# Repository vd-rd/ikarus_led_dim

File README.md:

## DC/DC linear dimmer for Power LEDS
3d view of the board available [here](https://a360.co/2TdbULz)

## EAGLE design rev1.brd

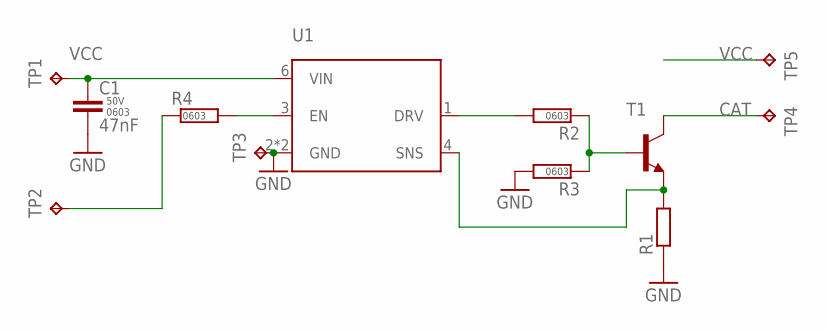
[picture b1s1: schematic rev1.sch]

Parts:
C1: 47nF; C0603; RATING 50V
R1: R-EU_R1206; R1206
R2, R3, R4: RES-0603; R0603
T1: BC868-NPN-SOT89-BCE; SOT89-BCE
TP1, TP2, TP3, TP4, TP5: TPB2,54; B2,54
U1: BCR450; SC74_INFINEON

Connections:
CAT: T1.C, TP4.TP
GND: C1.2, R1.1, R3.2, TP3.TP, U1.2 (GND), U1.5 (GND)
unnamed: R1.2, T1.E, U1.4 (SNS)
unnamed: R2.2, U1.1 (DRV)
unnamed: R4.2, U1.3 (EN)
unnamed: R2.1, R3.1, T1.B
unnamed: R4.1, TP2.TP
VCC: C1.1, TP1.TP, TP5.TP, U1.6 (VIN)

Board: 2 copper layers, 12 parts (0 on the bottom side), 8 nets, no tracks yet.

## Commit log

2019-03-03 added docs
2019-03-03 added fusion360 link
